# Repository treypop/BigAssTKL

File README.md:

# BigAssTKL

This is a TKL keyboard that uses the big ass enter style of enter key. It uses the steelseries 6gv2 version of the big ass enter key. It uses a Nice!nano for the microcontroller.

This project is still a work in progress.

# Refence Links
USB Daughter Board:  https://www.aliexpress.com/item/32967652914.html

Case:  https://www.aliexpress.com/item/32617566709.html

Plate: https://mechanicalkeyboards.com/shop/index.php?l=product_detail&p=2552

Spacer: https://geekhack.org/index.php?topic=100595.0

LED:  https://www.digikey.com/product-detail/en/yageo/MFR-25FBF52-10K/10.0KXBK-ND/13219

Resistor:  https://www.digikey.com/product-detail/en/yageo/MFR-25FBF52-10K/10.0KXBK-ND/13219

Nice!nano: https://docs.nicekeyboards.com/#/nice!nano/

Refrence PCB: https://github.com/kkatano/yurei

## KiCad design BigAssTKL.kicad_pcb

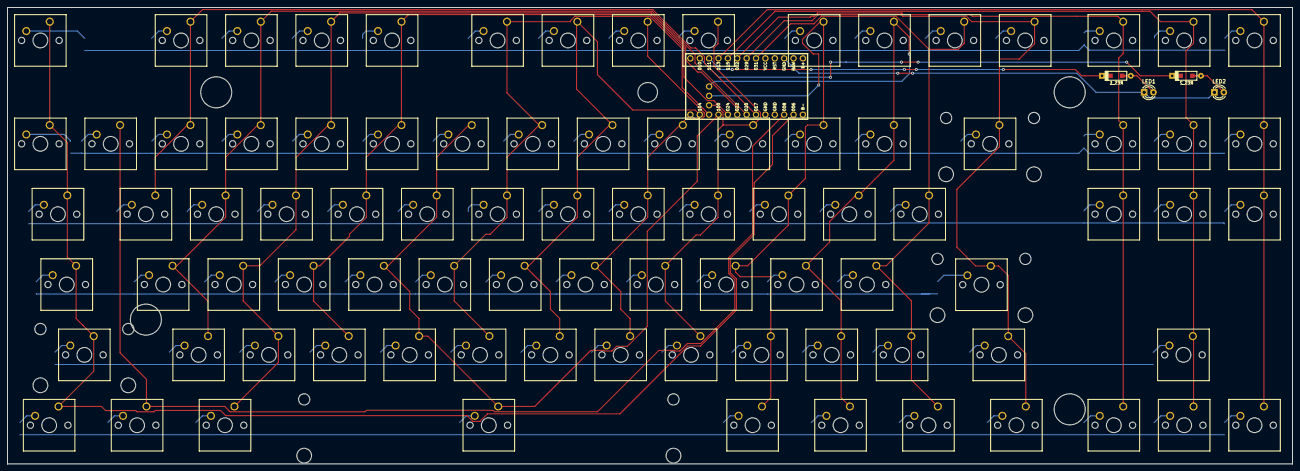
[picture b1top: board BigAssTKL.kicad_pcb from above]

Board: 2 copper layers, 347.9 x 123.5 mm, 178 parts (0 on the bottom side), 18 nets.

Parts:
A1: KEYSWITCH-PLAIN-MX-1U; SW_Cherry_MX_1.00u_PCB
ALT1, ALT2: KEYSWITCH-PLAIN-MX-1U; SW_Cherry_MX_1.25u_PCB
B1: KEYSWITCH-PLAIN-MX-1U; SW_Cherry_MX_1.00u_PCB
BACKSLASH1: KEYSWITCH-PLAIN-MX-1U; SW_Cherry_MX_1.00u_PCB
BACKSPACE1: KEYSWITCH-PLAIN-MX-2U; SW_Cherry_MX_2.00u_PCB
C1: KEYSWITCH-PLAIN-MX-1U; SW_Cherry_MX_1.00u_PCB
CAPSLOCK1: KEYSWITCH-PLAIN-MX-1U; SW_Cherry_MX_1.75u_PCB
COMMA1: KEYSWITCH-PLAIN-MX-1U; SW_Cherry_MX_1.00u_PCB
CTRL1, CTRL2: KEYSWITCH-PLAIN-MX-1U; SW_Cherry_MX_1.25u_PCB
D0, D1, D2, D3, D4, D5, D6, D7, D8, D9: DIODE-SOD-123; D_SOD-123_
D10: KEYSWITCH-PLAIN-MX-1U; SW_Cherry_MX_1.00u_PCB
DA1: DIODE-SOD-123; D_SOD-123_
DALT1, DALT2: DIODE-SOD-123; D_SOD-123_
DASH1: KEYSWITCH-PLAIN-MX-1U; SW_Cherry_MX_1.00u_PCB
DB1: DIODE-SOD-123; D_SOD-123_
DBACKSLASH1: DIODE-SOD-123; D_SOD-123_
DBACKSPACE1: DIODE-SOD-123; D_SOD-123_
DC1: DIODE-SOD-123; D_SOD-123_
DCAPSLOCK1: DIODE-SOD-123; D_SOD-123_
DCOMMA1: DIODE-SOD-123; D_SOD-123_
DCTRL1, DCTRL2: DIODE-SOD-123; D_SOD-123_
DD1: DIODE-SOD-123; D_SOD-123_
DDASH1: DIODE-SOD-123; D_SOD-123_
DDELETE1: DIODE-SOD-123; D_SOD-123_
DDOWN1: DIODE-SOD-123; D_SOD-123_
DE1: DIODE-SOD-123; D_SOD-123_
DELETE1: KEYSWITCH-PLAIN-MX-1U; SW_Cherry_MX_1.00u_PCB
DEND1: DIODE-SOD-123; D_SOD-123_
DEQUAL1: DIODE-SOD-123; D_SOD-123_
DESC1: DIODE-SOD-123; D_SOD-123_
DF1, DF2, DF3, DF4, DF5, DF6, DF7, DF8, DF9, DF10, DF11, DF12, DF13: DIODE-SOD-123; D_SOD-123_
DFN1: DIODE-SOD-123; D_SOD-123_
DG1: DIODE-SOD-123; D_SOD-123_
DGRAVE1: DIODE-SOD-123; D_SOD-123_
DH1: DIODE-SOD-123; D_SOD-123_
DHOME1: DIODE-SOD-123; D_SOD-123_
DI1: DIODE-SOD-123; D_SOD-123_
DINSERT1: DIODE-SOD-123; D_SOD-123_
DJ1: DIODE-SOD-123; D_SOD-123_
DK1: DIODE-SOD-123; D_SOD-123_
DL1: DIODE-SOD-123; D_SOD-123_
DLBRACKET1: DIODE-SOD-123; D_SOD-123_
DLEFT1: DIODE-SOD-123; D_SOD-123_
DM1: DIODE-SOD-123; D_SOD-123_
DMENU1: DIODE-SOD-123; D_SOD-123_
DN1: DIODE-SOD-123; D_SOD-123_
DO1: DIODE-SOD-123; D_SOD-123_
DOWN1: KEYSWITCH-PLAIN-MX-1U; SW_Cherry_MX_1.00u_PCB
DP1: DIODE-SOD-123; D_SOD-123_
DPAUSE1: DIODE-SOD-123; D_SOD-123_
DPERIOD1: DIODE-SOD-123; D_SOD-123_
DPGDN1: DIODE-SOD-123; D_SOD-123_
DPGUP1: DIODE-SOD-123; D_SOD-123_
DPRTSC1: DIODE-SOD-123; D_SOD-123_
DQ1: DIODE-SOD-123; D_SOD-123_
DQUOTE1: DIODE-SOD-123; D_SOD-123_
DR1: DIODE-SOD-123; D_SOD-123_
DRBRACKET1: DIODE-SOD-123; D_SOD-123_
DRIGHT1: DIODE-SOD-123; D_SOD-123_
DS1: DIODE-SOD-123; D_SOD-123_
DSCROLLLOCK1: DIODE-SOD-123; D_SOD-123_
DSEMICOLON1: DIODE-SOD-123; D_SOD-123_
DSHIFT1, DSHIFT2: DIODE-SOD-123; D_SOD-123_
DSLASH1: DIODE-SOD-123; D_SOD-123_
DSPACE1: DIODE-SOD-123; D_SOD-123_
DT1: DIODE-SOD-123; D_SOD-123_
DTAB1: DIODE-SOD-123; D_SOD-123_
DU1: DIODE-SOD-123; D_SOD-123_
DUP1: DIODE-SOD-123; D_SOD-123_
DV1: DIODE-SOD-123; D_SOD-123_
DW1: DIODE-SOD-123; D_SOD-123_
DWIN1: DIODE-SOD-123; D_SOD-123_
DX1: DIODE-SOD-123; D_SOD-123_
DY1: DIODE-SOD-123; D_SOD-123_
DZ1: DIODE-SOD-123; D_SOD-123_
E1: KEYSWITCH-PLAIN-MX-1U; SW_Cherry_MX_1.00u_PCB
END1: KEYSWITCH-PLAIN-MX-1U; SW_Cherry_MX_1.00u_PCB
ENTERBOTTOM1: KEYSWITCH-PLAIN-MX-2U; SW_Cherry_MX_2.25u_PCB
EQUAL1: KEYSWITCH-PLAIN-MX-1U; SW_Cherry_MX_1.00u_PCB
ESC1: KEYSWITCH-PLAIN-MX-1U; SW_Cherry_MX_1.00u_PCB
F1, F2, F3, F4, F5, F6, F7, F8, F9, F10, F11, F12, F13: KEYSWITCH-PLAIN-MX-1U; SW_Cherry_MX_1.00u_PCB
FN1: KEYSWITCH-PLAIN-MX-1U; SW_Cherry_MX_1.25u_PCB
G1: KEYSWITCH-PLAIN-MX-1U; SW_Cherry_MX_1.00u_PCB
GRAVE1: KEYSWITCH-PLAIN-MX-1U; SW_Cherry_MX_1.00u_PCB
H1: KEYSWITCH-PLAIN-MX-1U; SW_Cherry_MX_1.00u_PCB
HOME1: KEYSWITCH-PLAIN-MX-1U; SW_Cherry_MX_1.00u_PCB
I1: KEYSWITCH-PLAIN-MX-1U; SW_Cherry_MX_1.00u_PCB
INSERT1: KEYSWITCH-PLAIN-MX-1U; SW_Cherry_MX_1.00u_PCB
J1: KEYSWITCH-PLAIN-MX-1U; SW_Cherry_MX_1.00u_PCB
K1: KEYSWITCH-PLAIN-MX-1U; SW_Cherry_MX_1.00u_PCB
L1: KEYSWITCH-PLAIN-MX-1U; SW_Cherry_MX_1.00u_PCB
LBRACKET1: KEYSWITCH-PLAIN-MX-1U; SW_Cherry_MX_1.00u_PCB
LED1, LED2: LED; LED_D3.0mm
LEFT1: KEYSWITCH-PLAIN-MX-1U; SW_Cherry_MX_1.00u_PCB
M1: KEYSWITCH-PLAIN-MX-1U; SW_Cherry_MX_1.00u_PCB
MCU: nice_nano
MENU1: KEYSWITCH-PLAIN-MX-1U; SW_Cherry_MX_1.25u_PCB
N1: KEYSWITCH-PLAIN-MX-1U; SW_Cherry_MX_1.00u_PCB
O1: KEYSWITCH-PLAIN-MX-1U; SW_Cherry_MX_1.00u_PCB
P1: KEYSWITCH-PLAIN-MX-1U; SW_Cherry_MX_1.00u_PCB
PAUSE1: KEYSWITCH-PLAIN-MX-1U; SW_Cherry_MX_1.00u_PCB
PERIOD1: KEYSWITCH-PLAIN-MX-1U; SW_Cherry_MX_1.00u_PCB
PGDN1: KEYSWITCH-PLAIN-MX-1U; SW_Cherry_MX_1.00u_PCB
PGUP1: KEYSWITCH-PLAIN-MX-1U; SW_Cherry_MX_1.00u_PCB
PRTSC1: KEYSWITCH-PLAIN-MX-1U; SW_Cherry_MX_1.00u_PCB
Q1: KEYSWITCH-PLAIN-MX-1U; SW_Cherry_MX_1.00u_PCB
QUOTE1: KEYSWITCH-PLAIN-MX-1U; SW_Cherry_MX_1.00u_PCB
R1: KEYSWITCH-PLAIN-MX-1U; SW_Cherry_MX_1.00u_PCB
RBRACKET1: KEYSWITCH-PLAIN-MX-1U; SW_Cherry_MX_1.00u_PCB
RES_1, RES_2: 10k; D_SOD123_axial
RIGHT1: KEYSWITCH-PLAIN-MX-1U; SW_Cherry_MX_1.00u_PCB
S1: KEYSWITCH-PLAIN-MX-1U; SW_Cherry_MX_1.00u_PCB
SCROLLLOCK1: KEYSWITCH-PLAIN-MX-1U; SW_Cherry_MX_1.00u_PCB
SEMICOLON1: KEYSWITCH-PLAIN-MX-1U; SW_Cherry_MX_1.00u_PCB
SHIFT1: KEYSWITCH-PLAIN-MX-2U; SW_Cherry_MX_2.25u_PCB
SHIFT2: KEYSWITCH-PLAIN-MX-1U; SW_Cherry_MX_1.75u_PCB
SLASH1: KEYSWITCH-PLAIN-MX-1U; SW_Cherry_MX_1.00u_PCB
SPACE1: KEYSWITCH-PLAIN-MX-6.25U; SW_Cherry_MX_6.25u_PCB
T1: KEYSWITCH-PLAIN-MX-1U; SW_Cherry_MX_1.00u_PCB
TAB1: KEYSWITCH-PLAIN-MX-1U; SW_Cherry_MX_1.50u_PCB
U1: KEYSWITCH-PLAIN-MX-1U; SW_Cherry_MX_1.00u_PCB
UNK0, UNK1, UNK2, UNK3, UNK4, UNK5, UNK6, UNK7, UNK8, UNK9: KEYSWITCH-PLAIN-MX-1U; SW_Cherry_MX_1.00u_PCB
UP1: KEYSWITCH-PLAIN-MX-1U; SW_Cherry_MX_1.00u_PCB
V1: KEYSWITCH-PLAIN-MX-1U; SW_Cherry_MX_1.00u_PCB
W1: KEYSWITCH-PLAIN-MX-1U; SW_Cherry_MX_1.00u_PCB
WIN1: KEYSWITCH-PLAIN-MX-1U; SW_Cherry_MX_1.25u_PCB
X1: KEYSWITCH-PLAIN-MX-1U; SW_Cherry_MX_1.00u_PCB
Y1: KEYSWITCH-PLAIN-MX-1U; SW_Cherry_MX_1.00u_PCB
Z1: KEYSWITCH-PLAIN-MX-1U; SW_Cherry_MX_1.00u_PCB

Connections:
unnamed: DELETE1.1, INSERT1.1, LEFT1.1, MCU.18, PRTSC1.1
unnamed: BACKSLASH1.1, F11.1, MCU.20, MENU1.1, QUOTE1.1, RBRACKET1.1
unnamed: EQUAL1.1, F10.1, FN1.1, LBRACKET1.1, MCU.33, SEMICOLON1.1, SLASH1.1
unnamed: ALT2.1, DASH1.1, F9.1, L1.1, MCU.32, P1.1, PERIOD1.1
unnamed: COMMA1.1, F8.1, K1.1, MCU.31, O1.1, UNK0.1
unnamed: BACKSPACE1.1, CTRL2.1, ENTERBOTTOM1.1, F12.1, MCU.19, SHIFT2.1
unnamed: F7.1, I1.1, J1.1, M1.1, MCU.12, UNK9.1
unnamed: MCU.16, PAUSE1.1, PGDN1.1, PGUP1.1, RIGHT1.1
unnamed: A1.1, F2.1, MCU.6, UNK3.1, W1.1, Z1.1
unnamed: F1.1, MCU.5, Q1.1, UNK2.1
unnamed: CAPSLOCK1.1, CTRL1.1, ESC1.1, GRAVE1.1, MCU.1, SHIFT1.1, TAB1.1
unnamed: MCU.2, UNK1.1, WIN1.1
unnamed: F6.1, H1.1, MCU.11, N1.1, U1.1, UNK8.1
unnamed: B1.1, F5.1, G1.1, MCU.10, UNK7.1, Y1.1
unnamed: F13.1, MCU.9, SPACE1.1, T1.1, UNK6.1, V1.1
unnamed: C1.1, D10.1, F4.1, MCU.8, R1.1, UNK5.1
unnamed: ALT1.1, E1.1, F3.1, MCU.7, S1.1, UNK4.1, X1.1
unnamed: DOWN1.1, END1.1, HOME1.1, MCU.17, SCROLLLOCK1.1, UP1.1
